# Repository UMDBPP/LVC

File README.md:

# LVC
Low Voltage Cutoff Hardware for LiPo Battery Protection

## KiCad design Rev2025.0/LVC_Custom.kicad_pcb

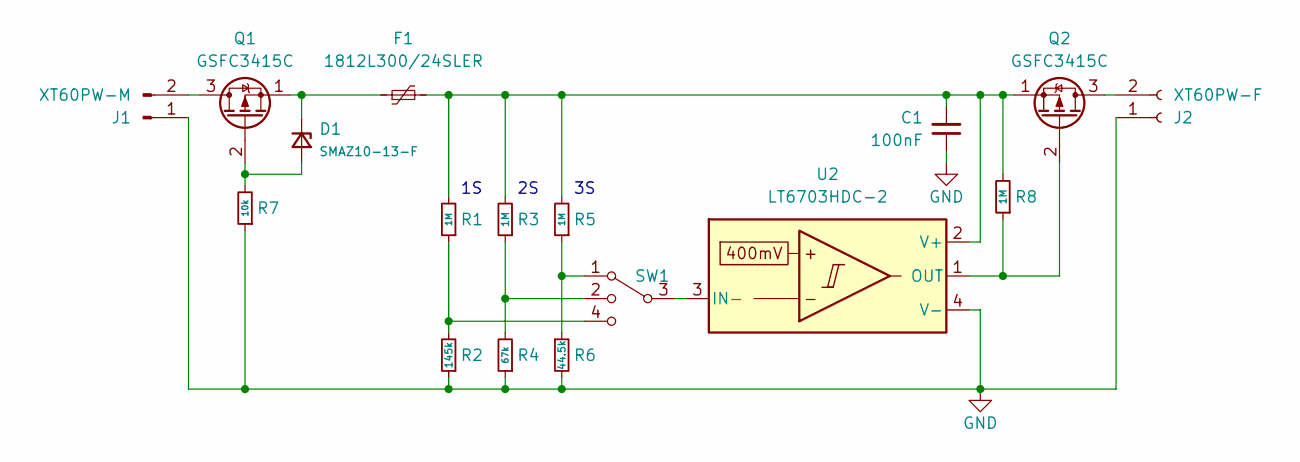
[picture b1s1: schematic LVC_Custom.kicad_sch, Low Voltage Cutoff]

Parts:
C1: 100nF; C_0603_1608Metric_Pad1.08x0.95mm_HandSolder
D1: SMAZ10-13-F; D_SMA_Handsoldering
F1: 1812L300/24SLER; Fuse_1812_4532Metric_Pad1.30x3.40mm_HandSolder
J1: XT60PW-M; AMASS_XT60PW-M_1x02_P7.20mm_Horizontal
J2: XT60PW-F; AMASS_XT60PW-F_1x02_P7.20mm_Horizontal
Q1, Q2: GSFC3415C; SOT-23-3
R1, R3, R5, R8: 1M; R_0603_1608Metric_Pad0.98x0.95mm_HandSolder
R2: 145k; R_0603_1608Metric_Pad0.98x0.95mm_HandSolder
R4: 67k; R_0603_1608Metric_Pad0.98x0.95mm_HandSolder
R6: 44.5k; R_0603_1608Metric_Pad0.98x0.95mm_HandSolder
R7: 10k; R_0603_1608Metric_Pad0.98x0.95mm_HandSolder
SW1: CUS-13TB; CUS-13TB_NDC
U2: LT6703HDC-2; DFN-3-1EP-2x2mm_P0.5mm_EP1x1.35mm

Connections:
GND: C1.1, J1.1, J2.1, R2.1, R4.1, R6.2, R7.1, U2.4 (V-)
unnamed: D1.2 (A), Q1.2 (G), R7.2
unnamed: D1.1 (K), F1.1, Q1.1 (S)
unnamed: J1.2, Q1.3 (D)
unnamed: J2.2, Q2.3 (D)
unnamed: Q2.2 (G), R8.1, U2.1 (OUT)
unnamed: C1.2, F1.2, Q2.1 (S), R1.2, R3.2, R5.2, R8.2, U2.2 (V+)
unnamed: R1.1, R2.2, SW1.4
unnamed: R3.1, R4.2, SW1.2
unnamed: R5.1, R6.1, SW1.1
unnamed: SW1.3, U2.3 (IN-)

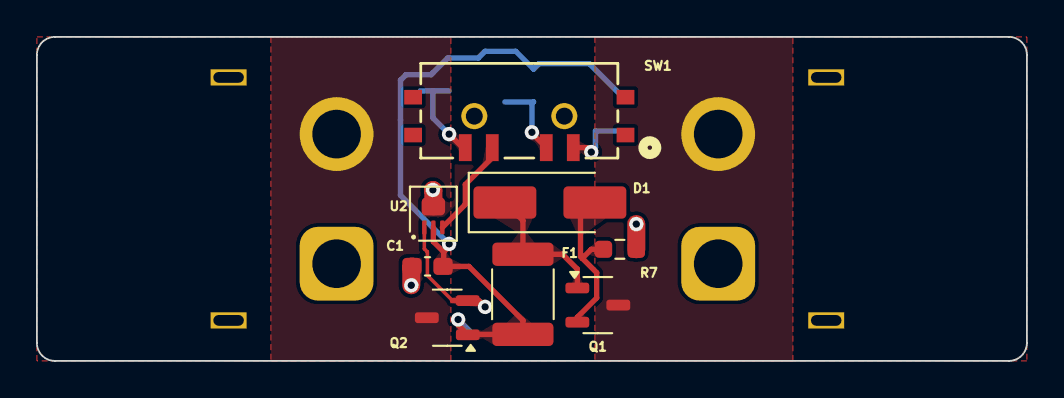
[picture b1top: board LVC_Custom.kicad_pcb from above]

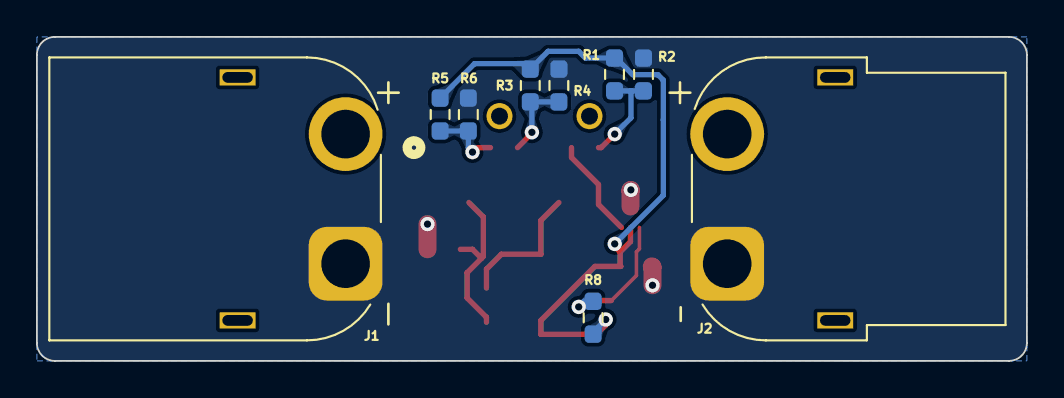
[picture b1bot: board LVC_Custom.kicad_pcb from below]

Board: 2 copper layers, 55.0 x 18.0 mm, 17 parts (9 on the bottom side), 11 nets.

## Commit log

2016-05-21 Rev 1.2 - added C3 to fix start/run switch
2016-05-21 Updated BOM for rev 1.2
2016-05-22 Fixed via error
2016-05-22 Added .gitignore
2016-05-22 Changed documentation error with T2
2016-05-22 Removed extraneous files
2016-05-22 Updated gitignore
2016-05-22 Removed eagle preferences file from git repository (contains data about local machine, not project)
2016-05-27 uploaded the current code for the LVC
2016-05-27 removed vim swap file
2016-05-27 Fixed typo
2016-06-27 rewrote for AVR C, as Arduino is the devil.
2017-05-09 created directory structure for ATTiny5 revision
2017-05-09 created program template, compile script
2017-05-09 initial code commit
2017-05-09 adc initialization
2017-05-09 revision 1 of tiny5 lvc code
2017-05-09 fixed potential error in lvc code
2017-05-09 clock is now set
2017-05-10 revision 2 of lvc code for tiny5
2017-06-27 Added more comments to tiny5 code
2017-07-08 Added resistor.lbr
2017-07-08 mcu lbr
2017-07-09 added voltage reg library
2017-07-09 second LDO added
2017-07-13 Added new choice of LDO
2017-07-14 updated software to reflect design changes
2017-07-14 program fixed to be within 512 bytes
2017-07-14 LDO added to schematic
2017-07-14 added supporting libraries
2017-07-14 added mcu block, updated libraries
2017-07-14 Went from adjustable to fixed voltage reg.
2017-07-22 Added op amp
2017-07-22 Added pin 1 mark to 8-MSOP package
2017-07-22 Added slide switch part
2017-07-22 library updates
2017-07-22 Added 3.5mm screw terminal part.
2017-07-22 Added zener diode.
2017-07-22 SQJ463EP transistor added
2017-07-22 added low-rung shit tier dual n-channel mosfet
2017-07-22 Added low-rung shit tier dual P-Channel MOSFET
2017-07-23 Prettified MOSFET symbols
2017-07-23 Added trimpot.
2017-07-23 Added LED
2017-07-23 added value and name to the package
2017-07-23 Added 50 mil header.
2017-07-23 Started layout
2017-07-23 added 2-pos switch
2017-07-24 Finished routing
2017-07-25 Prettified schematic
2017-10-04 updated schematic for reverse polarity protection
2017-10-05 yet another transistor (P-FET) update
2017-10-06 Routed new transistor. Cleaned up transistor package definition
2017-10-06 updated silkscreen, new renders, created gerbers
2017-10-24 fixed bug in lvc code
2018-03-10 1oz board
2018-03-10 gerbers
2018-03-16 Added Rev4
2018-03-16 Updated voltage divider resistor values
2018-03-19 Added comparator protection; cleaned up schematic
2018-03-26 Added Rev4 final
2018-04-30 Initial pass at Rev6 with buffer
    Buffer required to prevent voltage divider from driving the NFET directly, because evidently a few microamps of bias current is enough to ruin somebody's day.
2018-05-02 Updated buffer to be upstream of comparator
2018-05-07 Updated diode footprints
2018-05-07 Cleaned up Gerbers
2018-05-22 Cleaned up component naming on Rev 1
2018-05-22 Added rev 6.1; moved test point past buffer; cleaned up schematic
    Test point upstream of buffer caused observer effect due to multimeter input impedance
2018-05-23 Updated revision text on board
2025-04-04 2025 LVC revision 0, simpler than previous verisions
